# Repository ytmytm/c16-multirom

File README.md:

# C16 multirom

This project is a **multirom board for the Commodore 16 only**. It is heavily inspired by the [ROM update for Commodore 16](https://myoldcomputer.nl/other-computers/commodore-16/rom-update-commodore-16/) at My Old Computer.

The stock C16 uses **two separate chips** for BASIC and KERNAL. By putting **BASIC and KERNAL in a single 64K chip** (U3), we free the second socket for a **function ROM** (U4) e.g. 3-plus-1 and [Parobek](https://github.com/ytmytm/plus4-parobek), so the C16 gains capabilities similar to the Plus/4. Replacing the original mask ROMs with EEPROMs (e.g. 27E512) also reduces power draw.

**ROM switching**: each 64K chip holds two 32K images selected by address line A15. You can fix the choice with **switches** or **jumpers** on J1/J2 (closed = lower half, open = upper half), or add the optional **ATtiny85** to cycle through the four combinations with a long press on RESET.

## What you get

- **U3 (system ROM)**: One 64K chip with BASIC (same in both halves) and two kernals—e.g. stock in the lower 32K and JiffyDOS or 6510-patched in the upper 32K
- **U4 (function ROM)**: One 64K chip with **3-plus-1** in the lower 32K and **Parobek** in the upper 32K
- **Optional ATtiny85**: long-press RESET cycles U3 and U4 A15 through 00, 01, 10, 11 so you can change ROM set without opening the case or drilling holes for switches

## Hardware

The board is designed for the **C16** only. It plugs into the original ROM sockets (system and function) and uses:

- **U3**: 27C512 / 27E512 (64K) — system ROM (BASIC + two kernals in one chip).
- **U4**: 27C512 / 27E512 (64K) — function ROM (3-plus-1 + Parobek).
- **Glue logic**: 74LS00 (or HC/HCT).
- **Optional**: ATtiny85-20P for RESET long-press bank switching.

Precision pin headers plug into the existing socket footprints. Jumpers J1 and J2 set A15 on U3 and U4 to choose the active 32K half; you can wire switches to J1/J2 instead, or let the ATtiny control them.

### BOM

- 2× 28-pin DIP socket (for 27C512/27E512)
- 1× 8-pin DIP socket (for ATtiny85, if used)
- 1× 74LS00 or 74HCT00
- 2× 10K resistors
- 2× 2-pin pinheaders (J1, J2 — ROM half select)
- 2x14 + 1x1 - precision pinheaders (round gold pins) for mainboard socket connection
- 2× 27C512 or 27E512 (64K EPROM/EEPROM)
- 1× ATtiny85-20P (optional, for long-press bank switch)

### Assembly

1. Solder the precision pin headers so the board mates with the original ROM sockets (U3 and U4 positions on the C16 mainboard). Check orientation.
2. Solder resistors, 74LS00, and sockets. If using the ATtiny, program it with the firmware in `attiny/` and fit it. **Note:** The ATtiny firmware is untested.
3. Burn the two 64K ROM images to the EPROMs (see **ROM images** below). Put the system ROM in the new U3 and the function ROM in the new U4 (note that their positions are reversed when compared to the mainboard).
4. Set J1 and J2 (or leave them open for default halves). Power on and test.

**Note on PLA replacements:** If you use PLA replacements (daughterboards with GAL or CPLD) that are wider than a 28-pin DIL chip, the extra width can make the multirom board a tight fit. After soldering the sockets—but before plugging in any chips—you may want to use sandpaper to remove some material from the right-hand edge of the PCB so it fits better.

There are no traces on that side; you can cut right up to the actual pins of the new U4 socket, leaving them open like half-circles.

*In the photo: the yellow square marks the /BASIC line, which is not connected on J3 because J5 takes it from the mainboard socket (U3 pin 22). The green and purple rectangles show how the J3 /C0LOW and /C0HIGH lines are taken from U14 pins 5 and 11.*

## Project files (KiCad)

- [KiCad project](kicad-c16-multirom/)
- [Schematic PDF](kicad-c16-multirom/plots/kicad-c16-multirom.pdf)
- [Gerbers](kicad-c16-multirom/gerbers/) (or use the packaged zip in that folder for JLCPCB etc.)
  <!-- Order boards: <a href="https://www.pcbway.com/project/shareproject/...">PCBWay</a> -->
- [docs/](docs/) — additional documentation and notes.

## ROM images

The `rom/` directory contains a script and Makefile that build the 64K ROM images from public sources (Zimmers, Parobek, 6510 kernals). Downloads are done once; you choose PAL/NTSC and which kernals go in the lower and upper half of U3.

**Pre-built images** (built from this repo and published in the **Releases** section) are:

- **System ROM (PAL)** — BASIC + stock kernal in lower half, 6510-patched kernal in upper half. For U3; use when J1 is closed = stock, open = 6510.
- **System ROM (NTSC)** — Same layout for NTSC.
- **Function ROM** — 3-plus-1 in lower 32K, Parobek in upper 32K. Single image for U4; J2 closed = 3-plus-1, open = Parobek.

So you can burn one system ROM per region (PAL and NTSC) and one function ROM, and use jumpers or the ATtiny to switch.

### Building the ROMs yourself

From the `rom/` directory:

```sh
cd rom
make
```

Interactive mode will ask for TV standard (PAL/NTSC) and which kernal to use for the lower and upper half of U3 (stock, JiffyDOS, or 6510-patched). Default is stock in the lower half and JiffyDOS in the upper; 6510 kernals are downloaded automatically from hackjunk.com. JiffyDOS binaries (not redistributable) go in `rom/sources/jiffydos/`; see `rom/sources/jiffydos/README.txt`.

Non-interactive example (stock lower, JiffyDOS upper, PAL):

```sh
./build.sh --pal --kernal-lower=stock --kernal-upper=jiffydos
```

Outputs are `rom/out/u3-system.rom` and `rom/out/u4-function.rom`.

To build the **release** variants (stock+6510 PAL, stock+6510 NTSC, and the single function ROM):

```sh
make build-ni PAL=1 KERNAL_LOWER=stock KERNAL_UPPER=6510   # PAL system ROM
make build-ni PAL=0 KERNAL_LOWER=stock KERNAL_UPPER=6510   # NTSC system ROM
# Function ROM is always 3-plus-1 + Parobek (one image)
```

Then copy `out/u3-system.rom` and `out/u4-function.rom` to your release assets.

## Related

- [ROM update for Commodore 16](https://myoldcomputer.nl/other-computers/commodore-16/rom-update-commodore-16/) (My Old Computer) — main inspiration for this project.
- [Parobek ROM](https://github.com/ytmytm/plus4-parobek) — Function ROM with fast loader and extras for C16/+4; the upper half of U4 on this board holds Parobek.
- [C16 / Plus/4 — 8501 to 6510 CPU conversion](https://hackjunk.com/2017/06/23/commodore-16-plus-4-8501-to-6510-cpu-conversion/) — 6510-patched kernals (used in the release ROM builds) come from this project.
- [CBM firmware (Zimmers.net)](https://www.zimmers.net/anonftp/pub/cbm/firmware/computers/plus4/) — Stock BASIC, KERNAL, and 3-plus-1 ROM images; the `rom/` build script downloads from here.

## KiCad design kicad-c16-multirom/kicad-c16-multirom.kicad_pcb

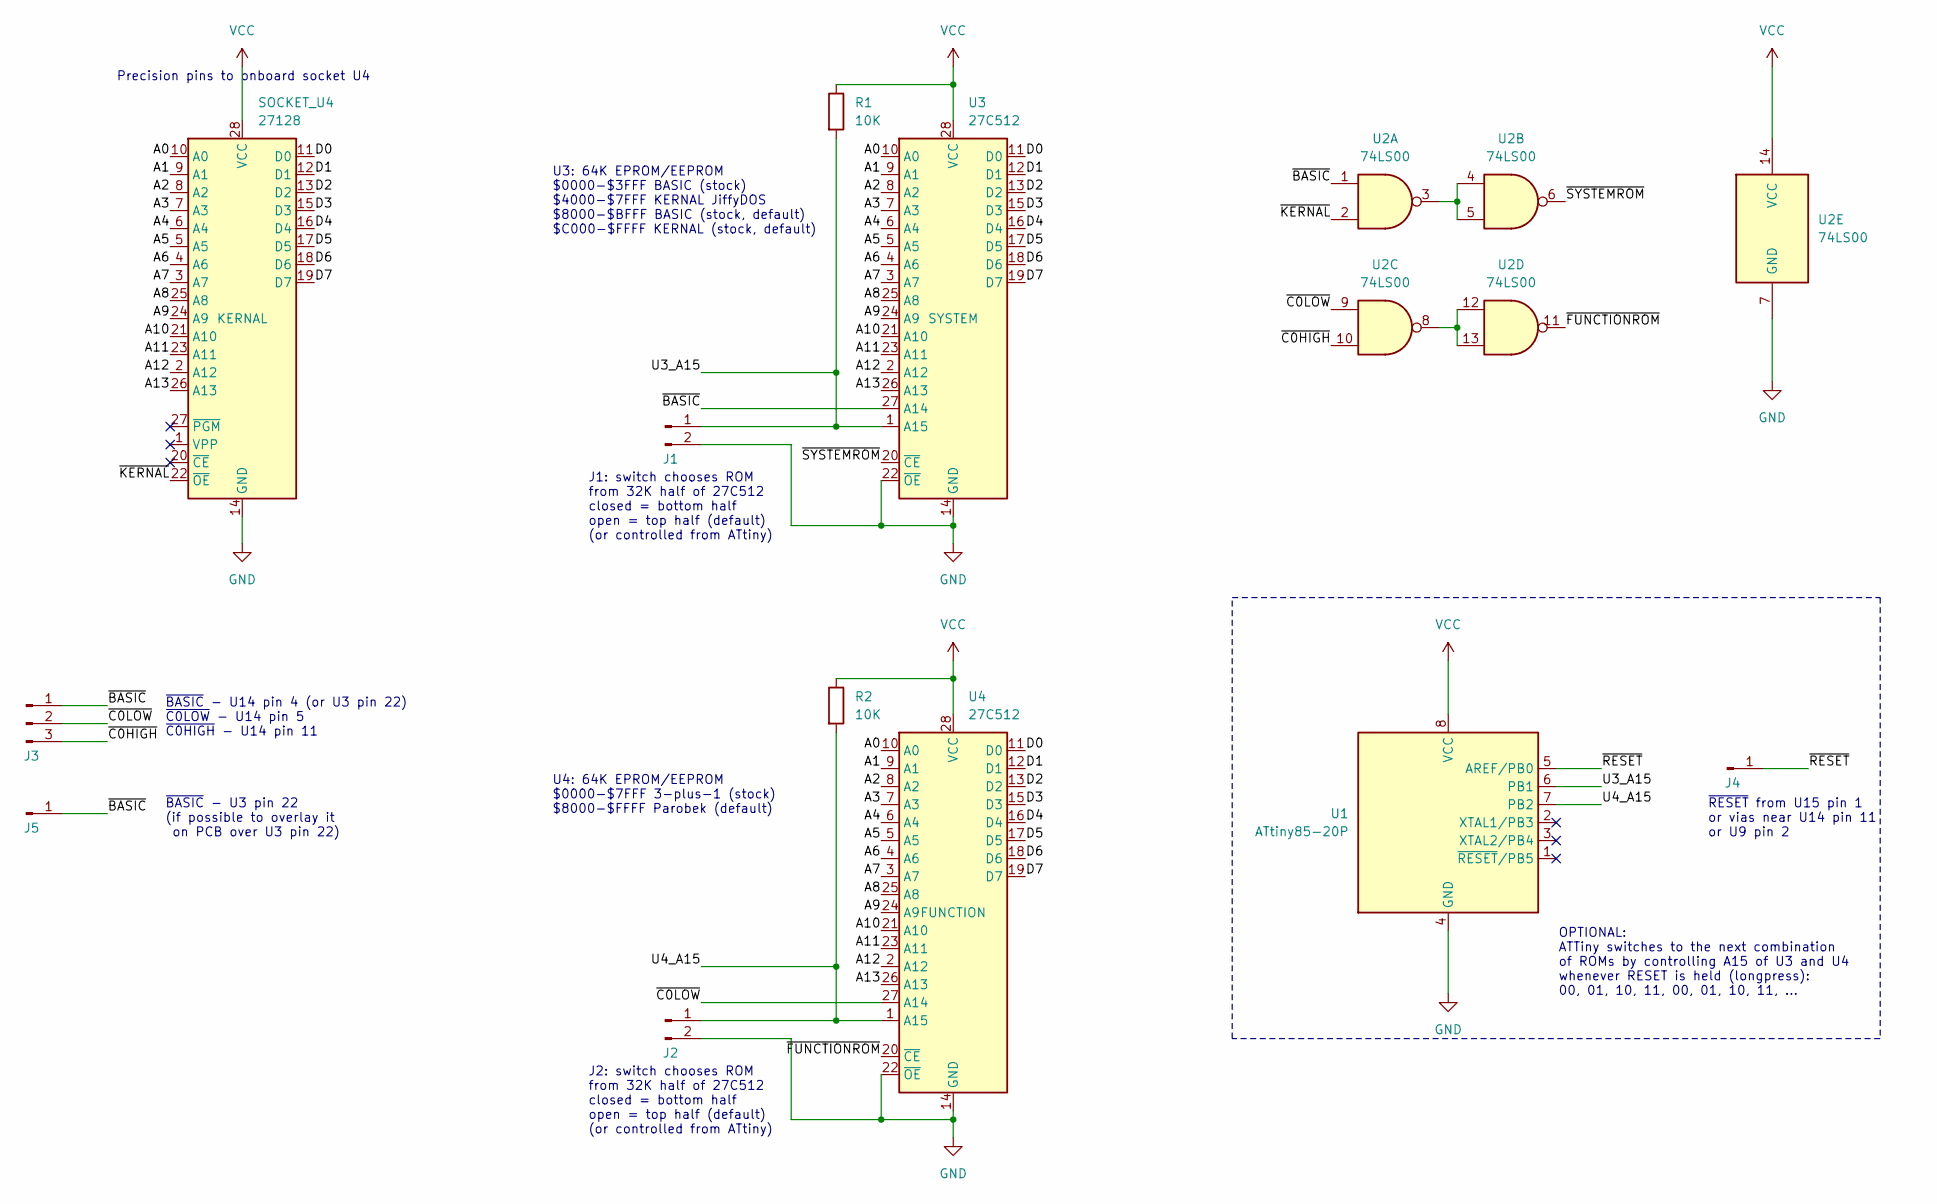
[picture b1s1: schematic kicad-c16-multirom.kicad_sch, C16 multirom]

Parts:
J1, J2: Conn_01x02_Pin; PinHeader_1x02_P2.54mm_Vertical
J3: Conn_01x01_Pin; PinHeader_1x03_P2.54mm_Vertical
J4, J5: Conn_01x01_Pin; PinHeader_1x01_P2.54mm_Vertical
R1, R2: 10K; R_Axial_DIN0207_L6.3mm_D2.5mm_P7.62mm_Horizontal
SOCKET_U4: 27128; DIP-28_W15.24mm_Socket
U1: ATtiny85-20P; DIP-8_W7.62mm_Socket_LongPads
U2: 74LS00; DIP-14_W7.62mm_Socket_LongPads
U3, U4: 27C512; DIP-28_W15.24mm_Socket_LongPads

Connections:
/A0: SOCKET_U4.10 (A0), U3.10 (A0), U4.10 (A0)
/A1: SOCKET_U4.9 (A1), U3.9 (A1), U4.9 (A1)
/A2: SOCKET_U4.8 (A2), U3.8 (A2), U4.8 (A2)
/A3: SOCKET_U4.7 (A3), U3.7 (A3), U4.7 (A3)
/A4: SOCKET_U4.6 (A4), U3.6 (A4), U4.6 (A4)
/A5: SOCKET_U4.5 (A5), U3.5 (A5), U4.5 (A5)
/A6: SOCKET_U4.4 (A6), U3.4 (A6), U4.4 (A6)
/A7: SOCKET_U4.3 (A7), U3.3 (A7), U4.3 (A7)
/A8: SOCKET_U4.25 (A8), U3.25 (A8), U4.25 (A8)
/A9: SOCKET_U4.24 (A9), U3.24 (A9), U4.24 (A9)
/A10: SOCKET_U4.21 (A10), U3.21 (A10), U4.21 (A10)
/A11: SOCKET_U4.23 (A11), U3.23 (A11), U4.23 (A11)
/A12: SOCKET_U4.2 (A12), U3.2 (A12), U4.2 (A12)
/A13: SOCKET_U4.26 (A13), U3.26 (A13), U4.26 (A13)
/D0: SOCKET_U4.11 (D0), U3.11 (D0), U4.11 (D0)
/D1: SOCKET_U4.12 (D1), U3.12 (D1), U4.12 (D1)
/D2: SOCKET_U4.13 (D2), U3.13 (D2), U4.13 (D2)
/D3: SOCKET_U4.15 (D3), U3.15 (D3), U4.15 (D3)
/D4: SOCKET_U4.16 (D4), U3.16 (D4), U4.16 (D4)
/D5: SOCKET_U4.17 (D5), U3.17 (D5), U4.17 (D5)
/D6: SOCKET_U4.18 (D6), U3.18 (D6), U4.18 (D6)
/D7: SOCKET_U4.19 (D7), U3.19 (D7), U4.19 (D7)
/U3_A15: J1.1, R1.2, U1.6 (PB1), U3.1 (A15)
/U4_A15: J2.1, R2.2, U1.7 (PB2), U4.1 (A15)
/~BASIC: J3.1, J5.1, U2.1, U3.27 (A14)
/~C0HIGH: J3.3, U2.10
/~C0LOW: J3.2, U2.9, U4.27 (A14)
/~FUNCTIONROM: U2.11, U4.20 (~CE)
/~KERNAL: SOCKET_U4.22 (~OE), U2.2
/~RESET: J4.1, U1.5 (AREF/PB0)
/~SYSTEMROM: U2.6, U3.20 (~CE)
GND: J1.2, J2.2, SOCKET_U4.14 (GND), U1.4 (GND), U2.7 (GND), U3.14 (GND), U3.22 (~OE), U4.14 (GND), U4.22 (~OE)
unnamed: U2.3, U2.4, U2.5
unnamed: U2.8, U2.12, U2.13
VCC: R1.1, R2.1, SOCKET_U4.28 (VCC), U1.8 (VCC), U2.14 (VCC), U3.28 (VCC), U4.28 (VCC)

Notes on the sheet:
~{RESET} from U15 pin 1 or vias near U14 pin 11 or U9 pin 2
U3: 64K EPROM/EEPROM $0000-$3FFF BASIC (stock) $4000-$7FFF KERNAL JiffyDOS $8000-$BFFF BASIC (stock, default) $C000-$FFFF KERNAL (stock, default)
U4: 64K EPROM/EEPROM $0000-$7FFF 3-plus-1 (stock) $8000-$FFFF Parobek (default)
Precision pins to onboard socket U4
~{BASIC} - U3 pin 22 (if possible to overlay it on PCB over U3 pin 22)
J2: switch chooses ROM from 32K half of 27C512 closed = bottom half open = top half (default) (or controlled from ATtiny)
J1: switch chooses ROM from 32K half of 27C512 closed = bottom half open = top half (default) (or controlled from ATtiny)
OPTIONAL: ATTiny switches to the next combination of ROMs by controlling A15 of U3 and U4 whenever RESET is held (longpress): 00, 01, 10, 11, 00, 01, 10, 11, ...
~{BASIC} - U14 pin 4 (or U3 pin 22) ~{C0LOW} - U14 pin 5 ~{C0HIGH} - U14 pin 11

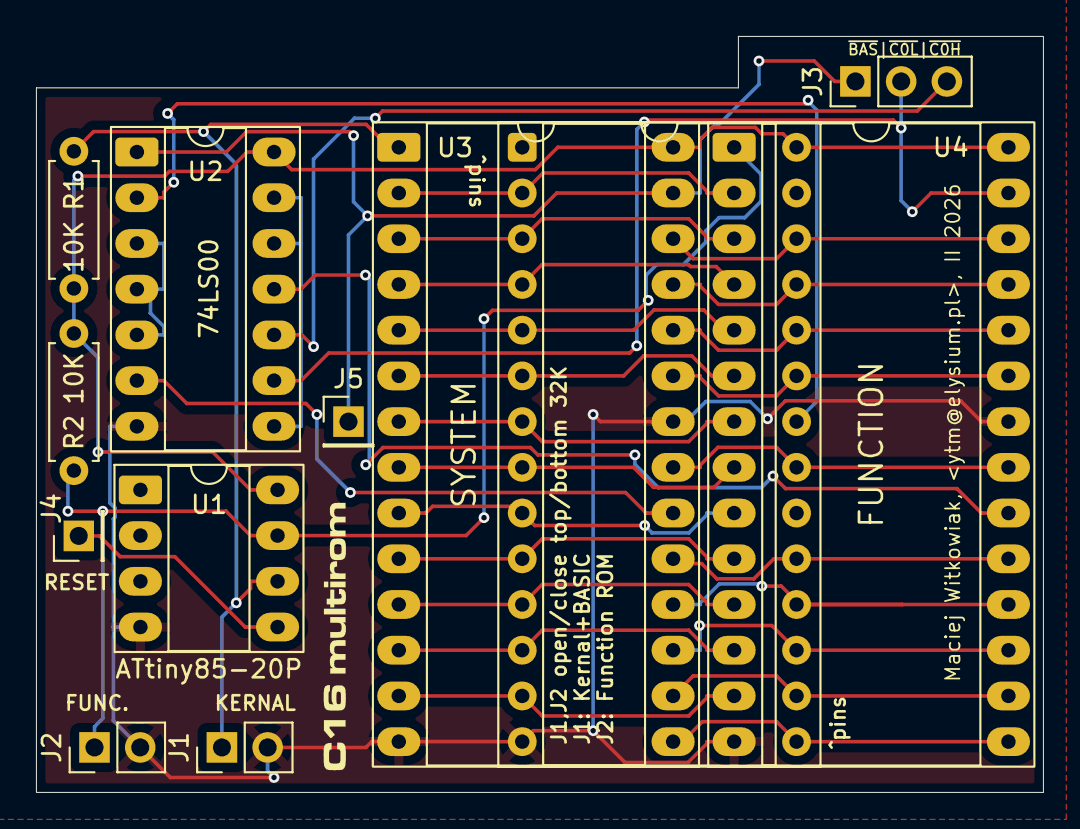
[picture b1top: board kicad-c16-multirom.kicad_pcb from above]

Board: 2 copper layers, 55.9 x 42.0 mm, 13 parts (0 on the bottom side), 35 nets.

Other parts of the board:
kibuzzard-6987CFF9: G***; kibuzzard-6987CFF9

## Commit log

2026-02-24 top-level .gitignore
2026-02-24 correct reference image placement, lock footprints for precision pins that go down to the mainboard
2026-02-24 Update README with PLA replacement note and add PCB reference image
2026-02-24 Update README to include note on untested ATtiny firmware and add installation reference image
2026-02-24 Refactor BASIC handling in build.sh to eliminate intermediate files and streamline ROM building process. Update Makefile to remove references to deleted .basic* files.
2026-02-24 NTSC Kernal from zimmers.net
2026-03-07 ATTiny code updated and tested, clarified on schematics how to connect /RESET line
